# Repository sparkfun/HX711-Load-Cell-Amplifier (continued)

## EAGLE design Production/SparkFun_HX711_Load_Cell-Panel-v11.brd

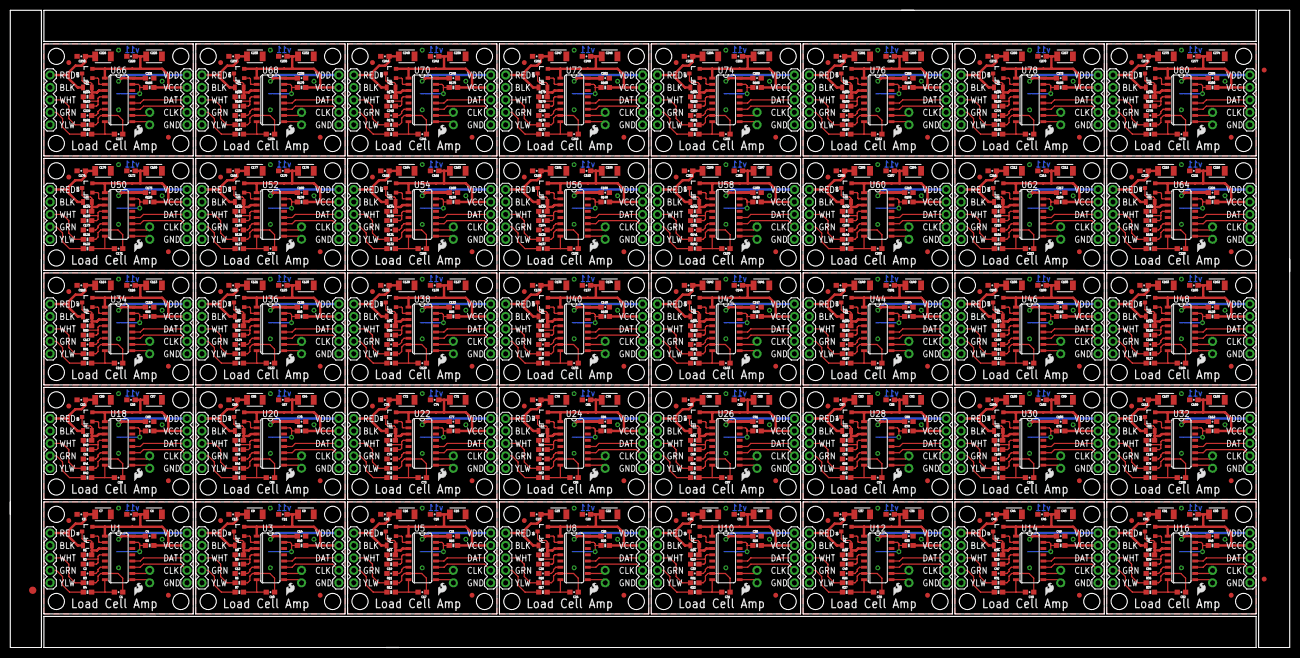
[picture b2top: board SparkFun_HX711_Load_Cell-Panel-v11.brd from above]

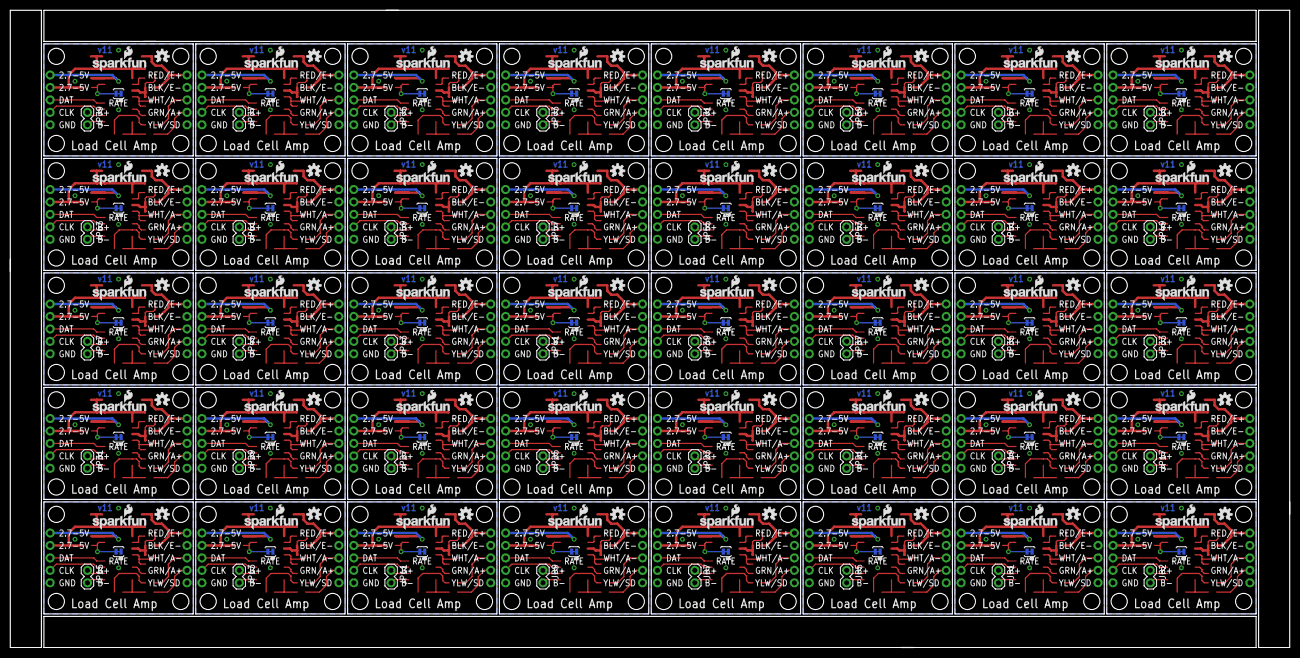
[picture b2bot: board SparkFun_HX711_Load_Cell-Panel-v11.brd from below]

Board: 2 copper layers, 261.1 x 130.0 mm, 1123 parts (160 on the bottom side), 680 nets.

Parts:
C1, C2, C3, C4, C5, C10, C11, C12, C13, C14, C17, C18, C19, C20, C21, C24, C25, C26, C27, C28, C31, C32, C33, C34, C35, C38, C39, C40, C41, C42, C45, C46, C47, C48, C49, C52, C53, C54, C55, C56, C59, C60, C61, C62, C63, C66, C67, C68, C69, C70, C73, C74, C75, C76, C77, C80, C81, C82, C83, C84, C87, C88, C89, C90, C91, C94, C95, C96, C97, C98, C101, C102, C103, C104, C105, C108, C109, C110, C111, C112, C115, C116, C117, C118, C119, C122, C123, C124, C125, C126, C129, C130, C131, C132, C133, C136, C137, C138, C139, C140, C143, C144, C145, C146, C147, C150, C151, C152, C153, C154, C157, C158, C159, C160, C161, C164, C165, C166, C167, C168, C171, C172, C173, C174, C175, C178, C179, C180, C181, C182, C185, C186, C187, C188, C189, C192, C193, C194, C195, C196, C199, C200, C201, C202, C203, C206, C207, C208, C209, C210, C213, C214, C215, C216, C217, C220, C221, C222, C223, C224, C227, C228, C229, C230, C231, C234, C235, C236, C237, C238, C241, C242, C243, C244, C245, C248, C249, C250, C251, C252, C255, C256, C257, C258, C259, C262, C263, C264, C265, C266, C269, C270, C271, C272, C273, C276, C277, C278, C279, C280: 0.1uF; 0603-CAP
C6, C7, C8, C9, C15, C16, C22, C23, C29, C30, C36, C37, C43, C44, C50, C51, C57, C58, C64, C65, C71, C72, C78, C79, C85, C86, C92, C93, C99, C100, C106, C107, C113, C114, C120, C121, C127, C128, C134, C135, C141, C142, C148, C149, C155, C156, C162, C163, C169, C170, C176, C177, C183, C184, C190, C191, C197, C198, C204, C205, C211, C212, C218, C219, C225, C226, C232, C233, C239, C240, C246, C247, C253, C254, C260, C261, C267, C268, C274, C275: 10uF; 1210
E$1: FIDUCIAL-1.5X3
E$5, E$6: FIDUCIAL-1X2
FID1, FID2, FID3, FID4, FID5, FID6, FID7, FID8, FID9, FID10, FID11, FID12, FID13, FID14, FID15, FID16, FID17, FID18, FID19, FID20, FID21, FID22, FID23, FID24, FID25, FID26, FID27, FID28, FID29, FID30, FID31, FID32, FID33, FID34, FID35, FID36, FID37, FID38, FID39, FID40, FID41, FID42, FID43, FID44, FID45, FID46, FID47, FID48, FID49, FID50, FID51, FID52, FID53, FID54, FID55, FID56, FID57, FID58, FID59, FID60, FID61, FID62, FID63, FID64, FID65, FID66, FID67, FID68, FID69, FID70, FID71, FID72, FID73, FID74, FID75, FID76, FID77, FID78, FID79, FID80: FIDUCIAL1X2; FIDUCIAL-1X2
J1, J2, J3, J4, J5, J6, J7, J8, J9, J10, J11, J12, J13, J14, J15, J16, J17, J18, J19, J20, J21, J22, J23, J24, J25, J26, J27, J28, J29, J30, J31, J32, J33, J34, J35, J36, J37, J38, J39, J40: 1X05
JP1, JP2, JP5, JP7, JP9, JP11, JP13, JP15, JP17, JP19, JP21, JP23, JP25, JP27, JP29, JP31, JP33, JP35, JP37, JP39, JP41, JP43, JP45, JP47, JP49, JP51, JP53, JP55, JP57, JP59, JP61, JP63, JP65, JP67, JP69, JP71, JP73, JP75, JP77, JP79: 1X02
JP3, JP4, JP6, JP8, JP10, JP12, JP14, JP16, JP18, JP20, JP22, JP24, JP26, JP28, JP30, JP32, JP34, JP36, JP38, JP40, JP42, JP44, JP46, JP48, JP50, JP52, JP54, JP56, JP58, JP60, JP62, JP64, JP66, JP68, JP70, JP72, JP74, JP76, JP78, JP80: 1X05
L1, L2, L3, L4, L5, L6, L7, L8, L9, L10, L11, L12, L13, L14, L15, L16, L17, L18, L19, L20, L21, L22, L23, L24, L25, L26, L27, L28, L29, L30, L31, L32, L33, L34, L35, L36, L37, L38, L39, L40: 3.3uH; 0805
LOGO1, LOGO2, LOGO5, LOGO7, LOGO9, LOGO11, LOGO13, LOGO15, LOGO17, LOGO19, LOGO21, LOGO23, LOGO25, LOGO27, LOGO29, LOGO31, LOGO33, LOGO35, LOGO37, LOGO39, LOGO41, LOGO43, LOGO45, LOGO47, LOGO49, LOGO51, LOGO53, LOGO55, LOGO57, LOGO59, LOGO61, LOGO63, LOGO65, LOGO67, LOGO69, LOGO71, LOGO73, LOGO75, LOGO77, LOGO79: SFE_LOGO_NAME_FLAME.1_INCH; SFE_LOGO_NAME_FLAME_.1
LOGO3, LOGO4, LOGO6, LOGO8, LOGO10, LOGO12, LOGO14, LOGO16, LOGO18, LOGO20, LOGO22, LOGO24, LOGO26, LOGO28, LOGO30, LOGO32, LOGO34, LOGO36, LOGO38, LOGO40, LOGO42, LOGO44, LOGO46, LOGO48, LOGO50, LOGO52, LOGO54, LOGO56, LOGO58, LOGO60, LOGO62, LOGO64, LOGO66, LOGO68, LOGO70, LOGO72, LOGO74, LOGO76, LOGO78, LOGO80: SFE_LOGO_FLAME.1_INCH; SFE_LOGO_FLAME_.1
Q1, Q2, Q3, Q4, Q5, Q6, Q7, Q8, Q9, Q10, Q11, Q12, Q13, Q14, Q15, Q16, Q17, Q18, Q19, Q20, Q21, Q22, Q23, Q24, Q25, Q26, Q27, Q28, Q29, Q30, Q31, Q32, Q33, Q34, Q35, Q36, Q37, Q38, Q39, Q40: MMBT4403; SOT23-3
R1, R9, R14, R19, R24, R29, R34, R39, R44, R49, R54, R59, R64, R69, R74, R79, R84, R89, R94, R99, R104, R109, R114, R119, R124, R129, R134, R139, R144, R149, R154, R159, R164, R169, R174, R179, R184, R189, R194, R199: 20k; 0603-RES
R2, R8, R13, R18, R23, R28, R33, R38, R43, R48, R53, R58, R63, R68, R73, R78, R83, R88, R93, R98, R103, R108, R113, R118, R123, R128, R133, R138, R143, R148, R153, R158, R163, R168, R173, R178, R183, R188, R193, R198: 8.2K; 0603-RES
R3, R4, R6, R7, R11, R12, R16, R17, R21, R22, R26, R27, R31, R32, R36, R37, R41, R42, R46, R47, R51, R52, R56, R57, R61, R62, R66, R67, R71, R72, R76, R77, R81, R82, R86, R87, R91, R92, R96, R97, R101, R102, R106, R107, R111, R112, R116, R117, R121, R122, R126, R127, R131, R132, R136, R137, R141, R142, R146, R147, R151, R152, R156, R157, R161, R162, R166, R167, R171, R172, R176, R177, R181, R182, R186, R187, R191, R192, R196, R197: 100; 0603-RES
R5, R10, R15, R20, R25, R30, R35, R40, R45, R50, R55, R60, R65, R70, R75, R80, R85, R90, R95, R100, R105, R110, R115, R120, R125, R130, R135, R140, R145, R150, R155, R160, R165, R170, R175, R180, R185, R190, R195, R200: 10K; 0603-RES
SJ1, SJ2, SJ3, SJ4, SJ5, SJ6, SJ7, SJ8, SJ9, SJ10, SJ11, SJ12, SJ13, SJ14, SJ15, SJ16, SJ17, SJ18, SJ19, SJ20, SJ21, SJ22, SJ23, SJ24, SJ25, SJ26, SJ27, SJ28, SJ29, SJ30, SJ31, SJ32, SJ33, SJ34, SJ35, SJ36, SJ37, SJ38, SJ39, SJ40: PAD-JUMPER-2-NC_BY_TRACE_YES_SILK
STANDOFF1, STANDOFF2, STANDOFF3, STANDOFF4, STANDOFF5, STANDOFF6, STANDOFF7, STANDOFF8, STANDOFF9, STANDOFF10, STANDOFF11, STANDOFF12, STANDOFF13, STANDOFF14, STANDOFF15, STANDOFF16, STANDOFF17, STANDOFF18, STANDOFF19, STANDOFF20, STANDOFF21, STANDOFF22, STANDOFF23, STANDOFF24, STANDOFF25, STANDOFF26, STANDOFF27, STANDOFF28, STANDOFF29, STANDOFF30, STANDOFF31, STANDOFF32, STANDOFF33, STANDOFF34, STANDOFF35, STANDOFF36, STANDOFF37, STANDOFF38, STANDOFF39, STANDOFF40, STANDOFF41, STANDOFF42, STANDOFF43, STANDOFF44, STANDOFF45, STANDOFF46, STANDOFF47, STANDOFF48, STANDOFF49, STANDOFF50, STANDOFF51, STANDOFF52, STANDOFF53, STANDOFF54, STANDOFF55, STANDOFF56, STANDOFF57, STANDOFF58, STANDOFF59, STANDOFF60, STANDOFF61, STANDOFF62, STANDOFF63, STANDOFF64, STANDOFF65, STANDOFF66, STANDOFF67, STANDOFF68, STANDOFF69, STANDOFF70, STANDOFF71, STANDOFF72, STANDOFF73, STANDOFF74, STANDOFF75, STANDOFF76, STANDOFF77, STANDOFF78, STANDOFF79, STANDOFF80, STANDOFF81, STANDOFF82, STANDOFF83, STANDOFF84, STANDOFF85, STANDOFF86, STANDOFF87, STANDOFF88, STANDOFF89, STANDOFF90, STANDOFF91, STANDOFF92, STANDOFF93, STANDOFF94, STANDOFF95, STANDOFF96, STANDOFF97, STANDOFF98, STANDOFF99, STANDOFF100, STANDOFF101, STANDOFF102, STANDOFF103, STANDOFF104, STANDOFF105, STANDOFF106, STANDOFF107, STANDOFF108, STANDOFF109, STANDOFF110, STANDOFF111, STANDOFF112, STANDOFF113, STANDOFF114, STANDOFF115, STANDOFF116, STANDOFF117, STANDOFF118, STANDOFF119, STANDOFF120, STANDOFF121, STANDOFF122, STANDOFF123, STANDOFF124, STANDOFF125, STANDOFF126, STANDOFF127, STANDOFF128, STANDOFF129, STANDOFF130, STANDOFF131, STANDOFF132, STANDOFF133, STANDOFF134, STANDOFF135, STANDOFF136, STANDOFF137, STANDOFF138, STANDOFF139, STANDOFF140, STANDOFF141, STANDOFF142, STANDOFF143, STANDOFF144, STANDOFF145, STANDOFF146, STANDOFF147, STANDOFF148, STANDOFF149, STANDOFF150, STANDOFF151, STANDOFF152, STANDOFF153, STANDOFF154, STANDOFF155, STANDOFF156, STANDOFF157, STANDOFF158, STANDOFF159, STANDOFF160: STAND-OFF
U1, U3, U5, U8, U10, U12, U14, U16, U18, U20, U22, U24, U26, U28, U30, U32, U34, U36, U38, U40, U42, U44, U46, U48, U50, U52, U54, U56, U58, U60, U62, U64, U66, U68, U70, U72, U74, U76, U78, U80: HX711; SO16
U2, U4, U6, U7, U9, U11, U13, U15, U17, U19, U21, U23, U25, U27, U29, U31, U33, U35, U37, U39, U41, U43, U45, U47, U49, U51, U53, U55, U57, U59, U61, U63, U65, U67, U69, U71, U73, U75, U77, U79: OSHW-LOGOS; OSHW-LOGO-S

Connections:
A+: JP4.2, R4.1
A+1: JP3.2, R7.1
A+2: JP6.2, R12.1
A+3: JP8.2, R17.1
A+4: JP10.2, R22.1
A+5: JP12.2, R27.1
A+6: JP14.2, R32.1
A+7: JP16.2, R37.1
A+8: JP18.2, R42.1
A+9: JP20.2, R47.1
A+10: JP22.2, R52.1
A+11: JP24.2, R57.1
A+12: JP26.2, R62.1
A+13: JP28.2, R67.1
A+14: JP30.2, R72.1
A+15: JP32.2, R77.1
A+16: JP34.2, R82.1
A+17: JP36.2, R87.1
A+18: JP38.2, R92.1
A+19: JP40.2, R97.1
A+20: JP42.2, R102.1
A+21: JP44.2, R107.1
A+22: JP46.2, R112.1
A+23: JP48.2, R117.1
A+24: JP50.2, R122.1
A+25: JP52.2, R127.1
A+26: JP54.2, R132.1
A+27: JP56.2, R137.1
A+28: JP58.2, R142.1
A+29: JP60.2, R147.1
A+30: JP62.2, R152.1
A+31: JP64.2, R157.1
A+32: JP66.2, R162.1
A+33: JP68.2, R167.1
A+34: JP70.2, R172.1
A+35: JP72.2, R177.1
A+36: JP74.2, R182.1
A+37: JP76.2, R187.1
A+38: JP78.2, R192.1
A+39: JP80.2, R197.1
A-: JP4.3, R3.1
A-1: JP3.3, R6.1
A-2: JP6.3, R11.1
A-3: JP8.3, R16.1
A-4: JP10.3, R21.1
A-5: JP12.3, R26.1
A-6: JP14.3, R31.1
A-7: JP16.3, R36.1
A-8: JP18.3, R41.1
A-9: JP20.3, R46.1
A-10: JP22.3, R51.1
A-11: JP24.3, R56.1
A-12: JP26.3, R61.1
A-13: JP28.3, R66.1
A-14: JP30.3, R71.1
A-15: JP32.3, R76.1
A-16: JP34.3, R81.1
A-17: JP36.3, R86.1
A-18: JP38.3, R91.1
A-19: JP40.3, R96.1
A-20: JP42.3, R101.1
A-21: JP44.3, R106.1
A-22: JP46.3, R111.1
A-23: JP48.3, R116.1
A-24: JP50.3, R121.1
A-25: JP52.3, R126.1
A-26: JP54.3, R131.1
A-27: JP56.3, R136.1
A-28: JP58.3, R141.1
A-29: JP60.3, R146.1
A-30: JP62.3, R151.1
A-31: JP64.3, R156.1
A-32: JP66.3, R161.1
A-33: JP68.3, R166.1
A-34: JP70.3, R171.1
A-35: JP72.3, R176.1
A-36: JP74.3, R181.1
A-37: JP76.3, R186.1
A-38: JP78.3, R191.1
A-39: JP80.3, R196.1
AVDD: C3.1, C7.1, JP4.5, L1.1
AVDD1: C9.1, C13.1, JP3.5, L2.1
AVDD2: C16.1, C20.1, JP6.5, L3.1
AVDD3: C23.1, C27.1, JP8.5, L4.1
AVDD4: C30.1, C34.1, JP10.5, L5.1
AVDD5: C37.1, C41.1, JP12.5, L6.1
AVDD6: C44.1, C48.1, JP14.5, L7.1
AVDD7: C51.1, C55.1, JP16.5, L8.1
AVDD8: C58.1, C62.1, JP18.5, L9.1
AVDD9: C65.1, C69.1, JP20.5, L10.1
AVDD10: C72.1, C76.1, JP22.5, L11.1
AVDD11: C79.1, C83.1, JP24.5, L12.1
AVDD12: C86.1, C90.1, JP26.5, L13.1
AVDD13: C93.1, C97.1, JP28.5, L14.1
AVDD14: C100.1, C104.1, JP30.5, L15.1
AVDD15: C107.1, C111.1, JP32.5, L16.1
AVDD16: C114.1, C118.1, JP34.5, L17.1
AVDD17: C121.1, C125.1, JP36.5, L18.1
AVDD18: C128.1, C132.1, JP38.5, L19.1
AVDD19: C135.1, C139.1, JP40.5, L20.1
AVDD20: C142.1, C146.1, JP42.5, L21.1
AVDD21: C149.1, C153.1, JP44.5, L22.1
AVDD22: C156.1, C160.1, JP46.5, L23.1
AVDD23: C163.1, C167.1, JP48.5, L24.1
AVDD24: C170.1, C174.1, JP50.5, L25.1
AVDD25: C177.1, C181.1, JP52.5, L26.1
AVDD26: C184.1, C188.1, JP54.5, L27.1
AVDD27: C191.1, C195.1, JP56.5, L28.1
AVDD28: C198.1, C202.1, JP58.5, L29.1
AVDD29: C205.1, C209.1, JP60.5, L30.1
AVDD30: C212.1, C216.1, JP62.5, L31.1
AVDD31: C219.1, C223.1, JP64.5, L32.1
AVDD32: C226.1, C230.1, JP66.5, L33.1
AVDD33: C233.1, C237.1, JP68.5, L34.1
AVDD34: C240.1, C244.1, JP70.5, L35.1
AVDD35: C247.1, C251.1, JP72.5, L36.1
AVDD36: C254.1, C258.1, JP74.5, L37.1
AVDD37: C261.1, C265.1, JP76.5, L38.1
AVDD38: C268.1, C272.1, JP78.5, L39.1
AVDD39: C275.1, C279.1, JP80.5, L40.1
B+: JP2.1, U1.10
B+1: JP1.1, U3.10
B+2: JP5.1, U5.10
B+3: JP7.1, U8.10
B+4: JP9.1, U10.10
B+5: JP11.1, U12.10
B+6: JP13.1, U14.10
B+7: JP15.1, U16.10
B+8: JP17.1, U18.10
B+9: JP19.1, U20.10
B+10: JP21.1, U22.10
B+11: JP23.1, U24.10
B+12: JP25.1, U26.10
B+13: JP27.1, U28.10
B+14: JP29.1, U30.10
B+15: JP31.1, U32.10
B+16: JP33.1, U34.10
B+17: JP35.1, U36.10
B+18: JP37.1, U38.10
B+19: JP39.1, U40.10
B+20: JP41.1, U42.10
B+21: JP43.1, U44.10
B+22: JP45.1, U46.10
B+23: JP47.1, U48.10
B+24: JP49.1, U50.10
B+25: JP51.1, U52.10
B+26: JP53.1, U54.10
B+27: JP55.1, U56.10
B+28: JP57.1, U58.10
B+29: JP59.1, U60.10
B+30: JP61.1, U62.10
B+31: JP63.1, U64.10
B+32: JP65.1, U66.10
B+33: JP67.1, U68.10
B+34: JP69.1, U70.10
B+35: JP71.1, U72.10
B+36: JP73.1, U74.10
B+37: JP75.1, U76.10
B+38: JP77.1, U78.10
B+39: JP79.1, U80.10
B-: JP2.2, U1.9
B-1: JP1.2, U3.9
B-2: JP5.2, U5.9
B-3: JP7.2, U8.9
B-4: JP9.2, U10.9
B-5: JP11.2, U12.9
B-6: JP13.2, U14.9
B-7: JP15.2, U16.9
B-8: JP17.2, U18.9
B-9: JP19.2, U20.9
B-10: JP21.2, U22.9
B-11: JP23.2, U24.9
B-12: JP25.2, U26.9
B-13: JP27.2, U28.9
B-14: JP29.2, U30.9
B-15: JP31.2, U32.9
B-16: JP33.2, U34.9
B-17: JP35.2, U36.9
B-18: JP37.2, U38.9
B-19: JP39.2, U40.9
B-20: JP41.2, U42.9
B-21: JP43.2, U44.9
B-22: JP45.2, U46.9
B-23: JP47.2, U48.9
B-24: JP49.2, U50.9
B-25: JP51.2, U52.9
B-26: JP53.2, U54.9
B-27: JP55.2, U56.9
B-28: JP57.2, U58.9
B-29: JP59.2, U60.9
B-30: JP61.2, U62.9
B-31: JP63.2, U64.9
B-32: JP65.2, U66.9
B-33: JP67.2, U68.9
B-34: JP69.2, U70.9
B-35: JP71.2, U72.9
B-36: JP73.2, U74.9
B-37: JP75.2, U76.9
B-38: JP77.2, U78.9
B-39: JP79.2, U80.9
DAT: J1.3, U1.12
DAT1: J2.3, U3.12
DAT2: J3.3, U5.12
DAT3: J4.3, U8.12
DAT4: J5.3, U10.12
DAT5: J6.3, U12.12
DAT6: J7.3, U14.12
DAT7: J8.3, U16.12
DAT8: J9.3, U18.12
DAT9: J10.3, U20.12
DAT10: J11.3, U22.12
DAT11: J12.3, U24.12
DAT12: J13.3, U26.12
DAT13: J14.3, U28.12
DAT14: J15.3, U30.12
DAT15: J16.3, U32.12
DAT16: J17.3, U34.12
DAT17: J18.3, U36.12
DAT18: J19.3, U38.12
DAT19: J20.3, U40.12
DAT20: J21.3, U42.12
DAT21: J22.3, U44.12
DAT22: J23.3, U46.12
DAT23: J24.3, U48.12
DAT24: J25.3, U50.12
DAT25: J26.3, U52.12
DAT26: J27.3, U54.12
DAT27: J28.3, U56.12
DAT28: J29.3, U58.12
DAT29: J30.3, U60.12
DAT30: J31.3, U62.12
DAT31: J32.3, U64.12
DAT32: J33.3, U66.12
DAT33: J34.3, U68.12
DAT34: J35.3, U70.12
DAT35: J36.3, U72.12
DAT36: J37.3, U74.12
DAT37: J38.3, U76.12
DAT38: J39.3, U78.12
DAT39: J40.3, U80.12
GND: C2.1, C3.2, C4.2, C5.2, C6.2, C7.2, J1.5, JP4.1, JP4.4, R2.1, SJ2.1, U1.5, U1.14
GND1: C8.2, C9.2, C11.2, C12.1, C13.2, C14.2, J2.5, JP3.1, JP3.4, R8.1, SJ1.1, U3.5, U3.14
GND2: C15.2, C16.2, C18.2, C19.1, C20.2, C21.2, J3.5, JP6.1, JP6.4, R13.1, SJ3.1, U5.5, U5.14
GND3: C22.2, C23.2, C25.2, C26.1, C27.2, C28.2, J4.5, JP8.1, JP8.4, R18.1, SJ4.1, U8.5, U8.14
GND4: C29.2, C30.2, C32.2, C33.1, C34.2, C35.2, J5.5, JP10.1, JP10.4, R23.1, SJ5.1, U10.5, U10.14
GND5: C36.2, C37.2, C39.2, C40.1, C41.2, C42.2, J6.5, JP12.1, JP12.4, R28.1, SJ6.1, U12.5, U12.14
GND6: C43.2, C44.2, C46.2, C47.1, C48.2, C49.2, J7.5, JP14.1, JP14.4, R33.1, SJ7.1, U14.5, U14.14
GND7: C50.2, C51.2, C53.2, C54.1, C55.2, C56.2, J8.5, JP16.1, JP16.4, R38.1, SJ8.1, U16.5, U16.14
GND8: C57.2, C58.2, C60.2, C61.1, C62.2, C63.2, J9.5, JP18.1, JP18.4, R43.1, SJ9.1, U18.5, U18.14
GND9: C64.2, C65.2, C67.2, C68.1, C69.2, C70.2, J10.5, JP20.1, JP20.4, R48.1, SJ10.1, U20.5, U20.14
GND10: C71.2, C72.2, C74.2, C75.1, C76.2, C77.2, J11.5, JP22.1, JP22.4, R53.1, SJ11.1, U22.5, U22.14
GND11: C78.2, C79.2, C81.2, C82.1, C83.2, C84.2, J12.5, JP24.1, JP24.4, R58.1, SJ12.1, U24.5, U24.14
GND12: C85.2, C86.2, C88.2, C89.1, C90.2, C91.2, J13.5, JP26.1, JP26.4, R63.1, SJ13.1, U26.5, U26.14
GND13: C92.2, C93.2, C95.2, C96.1, C97.2, C98.2, J14.5, JP28.1, JP28.4, R68.1, SJ14.1, U28.5, U28.14
GND14: C99.2, C100.2, C102.2, C103.1, C104.2, C105.2, J15.5, JP30.1, JP30.4, R73.1, SJ15.1, U30.5, U30.14
GND15: C106.2, C107.2, C109.2, C110.1, C111.2, C112.2, J16.5, JP32.1, JP32.4, R78.1, SJ16.1, U32.5, U32.14
GND16: C113.2, C114.2, C116.2, C117.1, C118.2, C119.2, J17.5, JP34.1, JP34.4, R83.1, SJ17.1, U34.5, U34.14
GND17: C120.2, C121.2, C123.2, C124.1, C125.2, C126.2, J18.5, JP36.1, JP36.4, R88.1, SJ18.1, U36.5, U36.14
GND18: C127.2, C128.2, C130.2, C131.1, C132.2, C133.2, J19.5, JP38.1, JP38.4, R93.1, SJ19.1, U38.5, U38.14
GND19: C134.2, C135.2, C137.2, C138.1, C139.2, C140.2, J20.5, JP40.1, JP40.4, R98.1, SJ20.1, U40.5, U40.14
GND20: C141.2, C142.2, C144.2, C145.1, C146.2, C147.2, J21.5, JP42.1, JP42.4, R103.1, SJ21.1, U42.5, U42.14
GND21: C148.2, C149.2, C151.2, C152.1, C153.2, C154.2, J22.5, JP44.1, JP44.4, R108.1, SJ22.1, U44.5, U44.14
GND22: C155.2, C156.2, C158.2, C159.1, C160.2, C161.2, J23.5, JP46.1, JP46.4, R113.1, SJ23.1, U46.5, U46.14
GND23: C162.2, C163.2, C165.2, C166.1, C167.2, C168.2, J24.5, JP48.1, JP48.4, R118.1, SJ24.1, U48.5, U48.14
GND24: C169.2, C170.2, C172.2, C173.1, C174.2, C175.2, J25.5, JP50.1, JP50.4, R123.1, SJ25.1, U50.5, U50.14
GND25: C176.2, C177.2, C179.2, C180.1, C181.2, C182.2, J26.5, JP52.1, JP52.4, R128.1, SJ26.1, U52.5, U52.14
GND26: C183.2, C184.2, C186.2, C187.1, C188.2, C189.2, J27.5, JP54.1, JP54.4, R133.1, SJ27.1, U54.5, U54.14
GND27: C190.2, C191.2, C193.2, C194.1, C195.2, C196.2, J28.5, JP56.1, JP56.4, R138.1, SJ28.1, U56.5, U56.14
GND28: C197.2, C198.2, C200.2, C201.1, C202.2, C203.2, J29.5, JP58.1, JP58.4, R143.1, SJ29.1, U58.5, U58.14
GND29: C204.2, C205.2, C207.2, C208.1, C209.2, C210.2, J30.5, JP60.1, JP60.4, R148.1, SJ30.1, U60.5, U60.14
GND30: C211.2, C212.2, C214.2, C215.1, C216.2, C217.2, J31.5, JP62.1, JP62.4, R153.1, SJ31.1, U62.5, U62.14
GND31: C218.2, C219.2, C221.2, C222.1, C223.2, C224.2, J32.5, JP64.1, JP64.4, R158.1, SJ32.1, U64.5, U64.14
GND32: C225.2, C226.2, C228.2, C229.1, C230.2, C231.2, J33.5, JP66.1, JP66.4, R163.1, SJ33.1, U66.5, U66.14
GND33: C232.2, C233.2, C235.2, C236.1, C237.2, C238.2, J34.5, JP68.1, JP68.4, R168.1, SJ34.1, U68.5, U68.14
GND34: C239.2, C240.2, C242.2, C243.1, C244.2, C245.2, J35.5, JP70.1, JP70.4, R173.1, SJ35.1, U70.5, U70.14
GND35: C246.2, C247.2, C249.2, C250.1, C251.2, C252.2, J36.5, JP72.1, JP72.4, R178.1, SJ36.1, U72.5, U72.14
GND36: C253.2, C254.2, C256.2, C257.1, C258.2, C259.2, J37.5, JP74.1, JP74.4, R183.1, SJ37.1, U74.5, U74.14
GND37: C260.2, C261.2, C263.2, C264.1, C265.2, C266.2, J38.5, JP76.1, JP76.4, R188.1, SJ38.1, U76.5, U76.14
GND38: C267.2, C268.2, C270.2, C271.1, C272.2, C273.2, J39.5, JP78.1, JP78.4, R193.1, SJ39.1, U78.5, U78.14
GND39: C274.2, C275.2, C277.2, C278.1, C279.2, C280.2, J40.5, JP80.1, JP80.4, R198.1, SJ40.1, U80.5, U80.14
unnamed: R5.1, SJ2.2, U1.15
unnamed: C1.1, R3.2, U1.7
unnamed: C1.2, R4.2, U1.8
unnamed: Q1.1, U1.2
unnamed: L1.2, Q1.3, R1.2, U1.3
unnamed: R1.1, R2.2, U1.4
unnamed: C2.2, U1.6
unnamed: Q2.1, U3.2
unnamed: R8.2, R9.1, U3.4
unnamed: C12.2, U3.6
unnamed: L2.2, Q2.3, R9.2, U3.3
unnamed: R10.1, SJ1.2, U3.15
unnamed: C10.1, R6.2, U3.7
unnamed: C10.2, R7.2, U3.8
unnamed: Q3.1, U5.2
unnamed: R13.2, R14.1, U5.4
unnamed: C19.2, U5.6
unnamed: L3.2, Q3.3, R14.2, U5.3
unnamed: R15.1, SJ3.2, U5.15
unnamed: C17.1, R11.2, U5.7
unnamed: C17.2, R12.2, U5.8
unnamed: Q4.1, U8.2
unnamed: R18.2, R19.1, U8.4
unnamed: C26.2, U8.6
unnamed: L4.2, Q4.3, R19.2, U8.3
unnamed: R20.1, SJ4.2, U8.15
unnamed: C24.1, R16.2, U8.7
unnamed: C24.2, R17.2, U8.8
unnamed: Q5.1, U10.2
unnamed: R23.2, R24.1, U10.4
unnamed: C33.2, U10.6
unnamed: L5.2, Q5.3, R24.2, U10.3
unnamed: R25.1, SJ5.2, U10.15
unnamed: C31.1, R21.2, U10.7
unnamed: C31.2, R22.2, U10.8
unnamed: Q6.1, U12.2
unnamed: R28.2, R29.1, U12.4
unnamed: C40.2, U12.6
unnamed: L6.2, Q6.3, R29.2, U12.3
unnamed: R30.1, SJ6.2, U12.15
unnamed: C38.1, R26.2, U12.7
unnamed: C38.2, R27.2, U12.8
unnamed: Q7.1, U14.2
unnamed: R33.2, R34.1, U14.4
unnamed: C47.2, U14.6
unnamed: L7.2, Q7.3, R34.2, U14.3
unnamed: R35.1, SJ7.2, U14.15
unnamed: C45.1, R31.2, U14.7
unnamed: C45.2, R32.2, U14.8
unnamed: Q8.1, U16.2
unnamed: R38.2, R39.1, U16.4
unnamed: C54.2, U16.6
unnamed: L8.2, Q8.3, R39.2, U16.3
unnamed: R40.1, SJ8.2, U16.15
unnamed: C52.1, R36.2, U16.7
unnamed: C52.2, R37.2, U16.8
unnamed: Q9.1, U18.2
unnamed: R43.2, R44.1, U18.4
unnamed: C61.2, U18.6
unnamed: L9.2, Q9.3, R44.2, U18.3
unnamed: R45.1, SJ9.2, U18.15
unnamed: C59.1, R41.2, U18.7
unnamed: C59.2, R42.2, U18.8
unnamed: Q10.1, U20.2
unnamed: R48.2, R49.1, U20.4
unnamed: C68.2, U20.6
unnamed: L10.2, Q10.3, R49.2, U20.3
unnamed: R50.1, SJ10.2, U20.15
unnamed: C66.1, R46.2, U20.7
unnamed: C66.2, R47.2, U20.8
unnamed: Q11.1, U22.2
unnamed: R53.2, R54.1, U22.4
unnamed: C75.2, U22.6
unnamed: L11.2, Q11.3, R54.2, U22.3
unnamed: R55.1, SJ11.2, U22.15
unnamed: C73.1, R51.2, U22.7
unnamed: C73.2, R52.2, U22.8
unnamed: Q12.1, U24.2
unnamed: R58.2, R59.1, U24.4
unnamed: C82.2, U24.6
unnamed: L12.2, Q12.3, R59.2, U24.3
unnamed: R60.1, SJ12.2, U24.15
unnamed: C80.1, R56.2, U24.7
unnamed: C80.2, R57.2, U24.8
unnamed: Q13.1, U26.2
unnamed: R63.2, R64.1, U26.4
unnamed: C89.2, U26.6
unnamed: L13.2, Q13.3, R64.2, U26.3
unnamed: R65.1, SJ13.2, U26.15
unnamed: C87.1, R61.2, U26.7
unnamed: C87.2, R62.2, U26.8
unnamed: Q14.1, U28.2
unnamed: R68.2, R69.1, U28.4
unnamed: C96.2, U28.6
unnamed: L14.2, Q14.3, R69.2, U28.3
unnamed: R70.1, SJ14.2, U28.15
unnamed: C94.1, R66.2, U28.7
unnamed: C94.2, R67.2, U28.8
unnamed: Q15.1, U30.2
unnamed: R73.2, R74.1, U30.4
unnamed: C103.2, U30.6
unnamed: L15.2, Q15.3, R74.2, U30.3
unnamed: R75.1, SJ15.2, U30.15
unnamed: C101.1, R71.2, U30.7
unnamed: C101.2, R72.2, U30.8
unnamed: Q16.1, U32.2
unnamed: R78.2, R79.1, U32.4
unnamed: C110.2, U32.6
unnamed: L16.2, Q16.3, R79.2, U32.3
unnamed: R80.1, SJ16.2, U32.15
unnamed: C108.1, R76.2, U32.7
unnamed: C108.2, R77.2, U32.8
unnamed: Q17.1, U34.2
unnamed: R83.2, R84.1, U34.4
unnamed: C117.2, U34.6
unnamed: L17.2, Q17.3, R84.2, U34.3
unnamed: R85.1, SJ17.2, U34.15
unnamed: C115.1, R81.2, U34.7
unnamed: C115.2, R82.2, U34.8
unnamed: Q18.1, U36.2
unnamed: R88.2, R89.1, U36.4
unnamed: C124.2, U36.6
unnamed: L18.2, Q18.3, R89.2, U36.3
unnamed: R90.1, SJ18.2, U36.15
unnamed: C122.1, R86.2, U36.7
unnamed: C122.2, R87.2, U36.8
unnamed: Q19.1, U38.2
unnamed: R93.2, R94.1, U38.4
unnamed: C131.2, U38.6
unnamed: L19.2, Q19.3, R94.2, U38.3
unnamed: R95.1, SJ19.2, U38.15
unnamed: C129.1, R91.2, U38.7
unnamed: C129.2, R92.2, U38.8
unnamed: Q20.1, U40.2
unnamed: R98.2, R99.1, U40.4
unnamed: C138.2, U40.6
unnamed: L20.2, Q20.3, R99.2, U40.3
unnamed: R100.1, SJ20.2, U40.15
unnamed: C136.1, R96.2, U40.7
unnamed: C136.2, R97.2, U40.8
unnamed: Q21.1, U42.2
unnamed: R103.2, R104.1, U42.4
unnamed: C145.2, U42.6
unnamed: L21.2, Q21.3, R104.2, U42.3
unnamed: R105.1, SJ21.2, U42.15
unnamed: C143.1, R101.2, U42.7
unnamed: C143.2, R102.2, U42.8
unnamed: Q22.1, U44.2
unnamed: R108.2, R109.1, U44.4
unnamed: C152.2, U44.6
unnamed: L22.2, Q22.3, R109.2, U44.3
unnamed: R110.1, SJ22.2, U44.15
unnamed: C150.1, R106.2, U44.7
unnamed: C150.2, R107.2, U44.8
unnamed: Q23.1, U46.2
unnamed: R113.2, R114.1, U46.4
unnamed: C159.2, U46.6
unnamed: L23.2, Q23.3, R114.2, U46.3
unnamed: R115.1, SJ23.2, U46.15
unnamed: C157.1, R111.2, U46.7
unnamed: C157.2, R112.2, U46.8
unnamed: Q24.1, U48.2
unnamed: R118.2, R119.1, U48.4
unnamed: C166.2, U48.6
unnamed: L24.2, Q24.3, R119.2, U48.3
unnamed: R120.1, SJ24.2, U48.15
unnamed: C164.1, R116.2, U48.7
unnamed: C164.2, R117.2, U48.8
unnamed: Q25.1, U50.2
unnamed: R123.2, R124.1, U50.4
unnamed: C173.2, U50.6
unnamed: L25.2, Q25.3, R124.2, U50.3
unnamed: R125.1, SJ25.2, U50.15
unnamed: C171.1, R121.2, U50.7
unnamed: C171.2, R122.2, U50.8
unnamed: Q26.1, U52.2
unnamed: R128.2, R129.1, U52.4
unnamed: C180.2, U52.6
unnamed: L26.2, Q26.3, R129.2, U52.3
unnamed: R130.1, SJ26.2, U52.15
unnamed: C178.1, R126.2, U52.7
unnamed: C178.2, R127.2, U52.8
unnamed: Q27.1, U54.2
unnamed: R133.2, R134.1, U54.4
unnamed: C187.2, U54.6
unnamed: L27.2, Q27.3, R134.2, U54.3
unnamed: R135.1, SJ27.2, U54.15
unnamed: C185.1, R131.2, U54.7
unnamed: C185.2, R132.2, U54.8
unnamed: Q28.1, U56.2
unnamed: R138.2, R139.1, U56.4
unnamed: C194.2, U56.6
unnamed: L28.2, Q28.3, R139.2, U56.3
unnamed: R140.1, SJ28.2, U56.15
unnamed: C192.1, R136.2, U56.7
unnamed: C192.2, R137.2, U56.8
unnamed: Q29.1, U58.2
unnamed: R143.2, R144.1, U58.4
unnamed: C201.2, U58.6
unnamed: L29.2, Q29.3, R144.2, U58.3
unnamed: R145.1, SJ29.2, U58.15
unnamed: C199.1, R141.2, U58.7
unnamed: C199.2, R142.2, U58.8
unnamed: Q30.1, U60.2
unnamed: R148.2, R149.1, U60.4
unnamed: C208.2, U60.6
unnamed: L30.2, Q30.3, R149.2, U60.3
unnamed: R150.1, SJ30.2, U60.15
unnamed: C206.1, R146.2, U60.7
unnamed: C206.2, R147.2, U60.8
unnamed: Q31.1, U62.2
unnamed: R153.2, R154.1, U62.4
unnamed: C215.2, U62.6
unnamed: L31.2, Q31.3, R154.2, U62.3
unnamed: R155.1, SJ31.2, U62.15
unnamed: C213.1, R151.2, U62.7
unnamed: C213.2, R152.2, U62.8
unnamed: Q32.1, U64.2
unnamed: R158.2, R159.1, U64.4
unnamed: C222.2, U64.6
unnamed: L32.2, Q32.3, R159.2, U64.3
unnamed: R160.1, SJ32.2, U64.15
unnamed: C220.1, R156.2, U64.7
unnamed: C220.2, R157.2, U64.8
unnamed: Q33.1, U66.2
unnamed: R163.2, R164.1, U66.4
unnamed: C229.2, U66.6
unnamed: L33.2, Q33.3, R164.2, U66.3
unnamed: R165.1, SJ33.2, U66.15
unnamed: C227.1, R161.2, U66.7
unnamed: C227.2, R162.2, U66.8
unnamed: Q34.1, U68.2
unnamed: R168.2, R169.1, U68.4
unnamed: C236.2, U68.6
unnamed: L34.2, Q34.3, R169.2, U68.3
unnamed: R170.1, SJ34.2, U68.15
unnamed: C234.1, R166.2, U68.7
unnamed: C234.2, R167.2, U68.8
unnamed: Q35.1, U70.2
unnamed: R173.2, R174.1, U70.4
unnamed: C243.2, U70.6
unnamed: L35.2, Q35.3, R174.2, U70.3
unnamed: R175.1, SJ35.2, U70.15
unnamed: C241.1, R171.2, U70.7
unnamed: C241.2, R172.2, U70.8
unnamed: Q36.1, U72.2
unnamed: R178.2, R179.1, U72.4
unnamed: C250.2, U72.6
unnamed: L36.2, Q36.3, R179.2, U72.3
unnamed: R180.1, SJ36.2, U72.15
unnamed: C248.1, R176.2, U72.7
unnamed: C248.2, R177.2, U72.8
unnamed: Q37.1, U74.2
unnamed: R183.2, R184.1, U74.4
unnamed: C257.2, U74.6
unnamed: L37.2, Q37.3, R184.2, U74.3
unnamed: R185.1, SJ37.2, U74.15
unnamed: C255.1, R181.2, U74.7
unnamed: C255.2, R182.2, U74.8
unnamed: Q38.1, U76.2
unnamed: R188.2, R189.1, U76.4
unnamed: C264.2, U76.6
unnamed: L38.2, Q38.3, R189.2, U76.3
unnamed: R190.1, SJ38.2, U76.15
unnamed: C262.1, R186.2, U76.7
unnamed: C262.2, R187.2, U76.8
unnamed: Q39.1, U78.2
unnamed: R193.2, R194.1, U78.4
unnamed: C271.2, U78.6
unnamed: L39.2, Q39.3, R194.2, U78.3
unnamed: R195.1, SJ39.2, U78.15
unnamed: C269.1, R191.2, U78.7
unnamed: C269.2, R192.2, U78.8
unnamed: Q40.1, U80.2
unnamed: R198.2, R199.1, U80.4
unnamed: C278.2, U80.6
unnamed: L40.2, Q40.3, R199.2, U80.3
unnamed: R200.1, SJ40.2, U80.15
unnamed: C276.1, R196.2, U80.7
unnamed: C276.2, R197.2, U80.8
SCK: J1.4, U1.11
SCK1: J2.4, U3.11
SCK2: J3.4, U5.11
SCK3: J4.4, U8.11
SCK4: J5.4, U10.11
SCK5: J6.4, U12.11
SCK6: J7.4, U14.11
SCK7: J8.4, U16.11
SCK8: J9.4, U18.11
SCK9: J10.4, U20.11
SCK10: J11.4, U22.11
SCK11: J12.4, U24.11
SCK12: J13.4, U26.11
SCK13: J14.4, U28.11
SCK14: J15.4, U30.11
SCK15: J16.4, U32.11
SCK16: J17.4, U34.11
SCK17: J18.4, U36.11
SCK18: J19.4, U38.11
SCK19: J20.4, U40.11
SCK20: J21.4, U42.11
SCK21: J22.4, U44.11
SCK22: J23.4, U46.11
SCK23: J24.4, U48.11
SCK24: J25.4, U50.11
SCK25: J26.4, U52.11
SCK26: J27.4, U54.11
SCK27: J28.4, U56.11
SCK28: J29.4, U58.11
SCK29: J30.4, U60.11
SCK30: J31.4, U62.11
SCK31: J32.4, U64.11
SCK32: J33.4, U66.11
SCK33: J34.4, U68.11
SCK34: J35.4, U70.11
SCK35: J36.4, U72.11
SCK36: J37.4, U74.11
SCK37: J38.4, U76.11
SCK38: J39.4, U78.11
SCK39: J40.4, U80.11
VCC: C5.1, C6.1, J1.2, Q1.2, R5.2, U1.1
VCC1: C8.1, C11.1, J2.2, Q2.2, R10.2, U3.1
VCC2: C15.1, C18.1, J3.2, Q3.2, R15.2, U5.1
VCC3: C22.1, C25.1, J4.2, Q4.2, R20.2, U8.1
VCC4: C29.1, C32.1, J5.2, Q5.2, R25.2, U10.1
VCC5: C36.1, C39.1, J6.2, Q6.2, R30.2, U12.1
VCC6: C43.1, C46.1, J7.2, Q7.2, R35.2, U14.1
VCC7: C50.1, C53.1, J8.2, Q8.2, R40.2, U16.1
VCC8: C57.1, C60.1, J9.2, Q9.2, R45.2, U18.1
VCC9: C64.1, C67.1, J10.2, Q10.2, R50.2, U20.1
VCC10: C71.1, C74.1, J11.2, Q11.2, R55.2, U22.1
VCC11: C78.1, C81.1, J12.2, Q12.2, R60.2, U24.1
VCC12: C85.1, C88.1, J13.2, Q13.2, R65.2, U26.1
VCC13: C92.1, C95.1, J14.2, Q14.2, R70.2, U28.1
VCC14: C99.1, C102.1, J15.2, Q15.2, R75.2, U30.1
VCC15: C106.1, C109.1, J16.2, Q16.2, R80.2, U32.1
VCC16: C113.1, C116.1, J17.2, Q17.2, R85.2, U34.1
VCC17: C120.1, C123.1, J18.2, Q18.2, R90.2, U36.1
VCC18: C127.1, C130.1, J19.2, Q19.2, R95.2, U38.1
VCC19: C134.1, C137.1, J20.2, Q20.2, R100.2, U40.1
VCC20: C141.1, C144.1, J21.2, Q21.2, R105.2, U42.1
VCC21: C148.1, C151.1, J22.2, Q22.2, R110.2, U44.1
VCC22: C155.1, C158.1, J23.2, Q23.2, R115.2, U46.1
VCC23: C162.1, C165.1, J24.2, Q24.2, R120.2, U48.1
VCC24: C169.1, C172.1, J25.2, Q25.2, R125.2, U50.1
VCC25: C176.1, C179.1, J26.2, Q26.2, R130.2, U52.1
VCC26: C183.1, C186.1, J27.2, Q27.2, R135.2, U54.1
VCC27: C190.1, C193.1, J28.2, Q28.2, R140.2, U56.1
VCC28: C197.1, C200.1, J29.2, Q29.2, R145.2, U58.1
VCC29: C204.1, C207.1, J30.2, Q30.2, R150.2, U60.1
VCC30: C211.1, C214.1, J31.2, Q31.2, R155.2, U62.1
VCC31: C218.1, C221.1, J32.2, Q32.2, R160.2, U64.1
VCC32: C225.1, C228.1, J33.2, Q33.2, R165.2, U66.1
VCC33: C232.1, C235.1, J34.2, Q34.2, R170.2, U68.1
VCC34: C239.1, C242.1, J35.2, Q35.2, R175.2, U70.1
VCC35: C246.1, C249.1, J36.2, Q36.2, R180.2, U72.1
VCC36: C253.1, C256.1, J37.2, Q37.2, R185.2, U74.1
VCC37: C260.1, C263.1, J38.2, Q38.2, R190.2, U76.1
VCC38: C267.1, C270.1, J39.2, Q39.2, R195.2, U78.1
VCC39: C274.1, C277.1, J40.2, Q40.2, R200.2, U80.1
VDD: C4.1, J1.1, U1.16
VDD1: C14.1, J2.1, U3.16
VDD2: C21.1, J3.1, U5.16
VDD3: C28.1, J4.1, U8.16
VDD4: C35.1, J5.1, U10.16
VDD5: C42.1, J6.1, U12.16
VDD6: C49.1, J7.1, U14.16
VDD7: C56.1, J8.1, U16.16
VDD8: C63.1, J9.1, U18.16
VDD9: C70.1, J10.1, U20.16
VDD10: C77.1, J11.1, U22.16
VDD11: C84.1, J12.1, U24.16
VDD12: C91.1, J13.1, U26.16
VDD13: C98.1, J14.1, U28.16
VDD14: C105.1, J15.1, U30.16
VDD15: C112.1, J16.1, U32.16
VDD16: C119.1, J17.1, U34.16
VDD17: C126.1, J18.1, U36.16
VDD18: C133.1, J19.1, U38.16
VDD19: C140.1, J20.1, U40.16
VDD20: C147.1, J21.1, U42.16
VDD21: C154.1, J22.1, U44.16
VDD22: C161.1, J23.1, U46.16
VDD23: C168.1, J24.1, U48.16
VDD24: C175.1, J25.1, U50.16
VDD25: C182.1, J26.1, U52.16
VDD26: C189.1, J27.1, U54.16
VDD27: C196.1, J28.1, U56.16
VDD28: C203.1, J29.1, U58.16
VDD29: C210.1, J30.1, U60.16
VDD30: C217.1, J31.1, U62.16
VDD31: C224.1, J32.1, U64.16
VDD32: C231.1, J33.1, U66.16
VDD33: C238.1, J34.1, U68.16
VDD34: C245.1, J35.1, U70.16
VDD35: C252.1, J36.1, U72.16
VDD36: C259.1, J37.1, U74.16
VDD37: C266.1, J38.1, U76.16
VDD38: C273.1, J39.1, U78.16
VDD39: C280.1, J40.1, U80.16
